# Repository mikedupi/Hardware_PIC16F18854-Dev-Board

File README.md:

# Hardware_PIC16F18854-Dev-Board
Desgined using KiCAD and designed for production at JLCPCB, with part numbers included from LCSC this board can be dropped into JLC's portal and delivered fully populated.

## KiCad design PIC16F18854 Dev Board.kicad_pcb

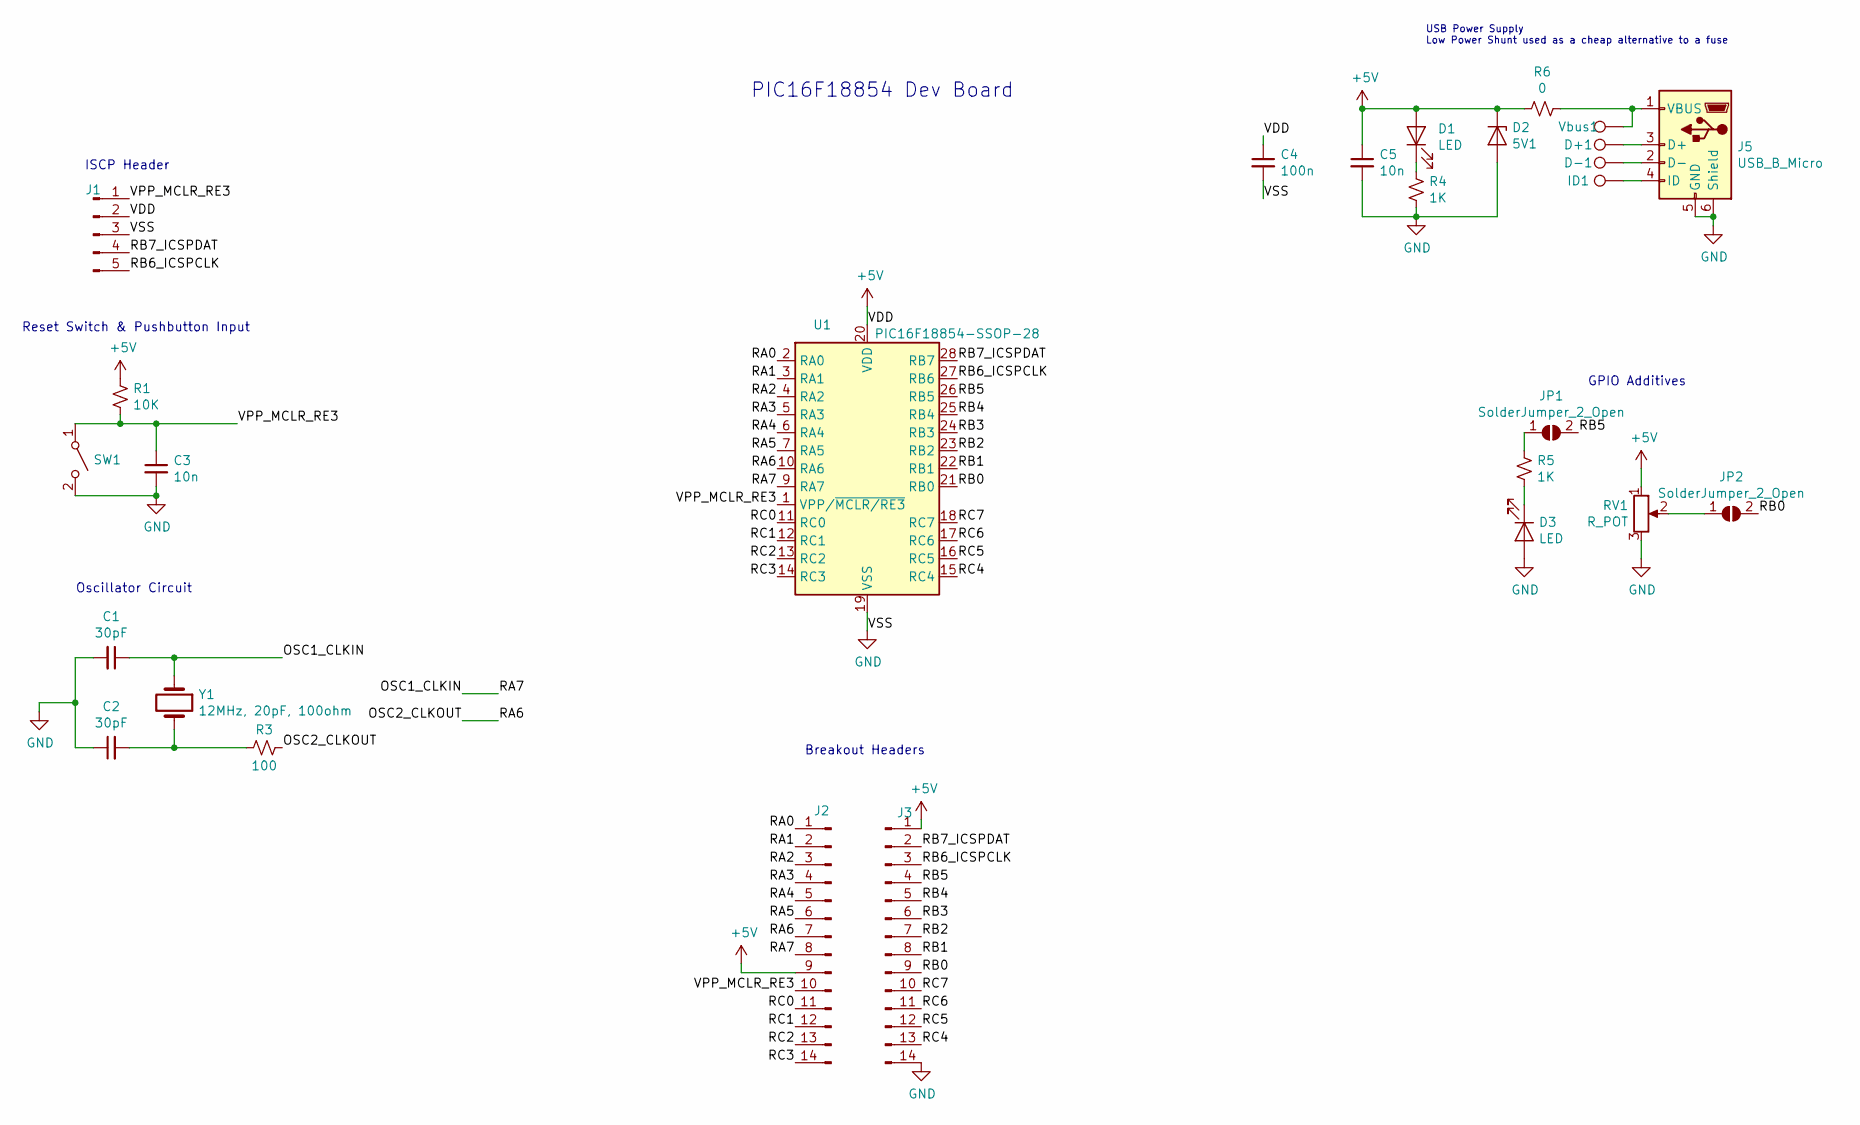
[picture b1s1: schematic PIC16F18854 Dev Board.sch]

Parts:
C1, C2: 30pF; C_0402_1005Metric; LCSC C1570
C3, C5: 10n; C_0402_1005Metric; LCSC C15195
C4: 100n; C_0402_1005Metric; LCSC C1525
D1, D3: LED; LED_0805_2012Metric; LCSC C2297
D2: 5V1; D_MiniMELF
D+1: TestPoint; TestPoint_Pad_D1.0mm
D-1: TestPoint; TestPoint_Pad_D1.0mm
ID1: TestPoint; TestPoint_Pad_D1.0mm
J1: Conn_01x05_Male; PinHeader_1x05_P2.54mm_Vertical
J2, J3: Conn_01x14_Male; PinHeader_1x14_P2.54mm_Vertical
J5: USB_B_Micro; USB_Micro-B_Amphenol_10103594-0001LF_Horizontal; LCSC C132563
JP1, JP2: SolderJumper_2_Open; SolderJumper-2_P1.3mm_Open_Pad1.0x1.5mm
R1: 10K; R_0402_1005Metric; LCSC C25744
R3: 100; R_0402_1005Metric; LCSC C25076
R4, R5: 1K; R_0402_1005Metric; LCSC C11702
R6: 0; R_0402_1005Metric; LCSC C17168
RV1: R_POT; Potentiometer_ACP_CA9-H2,5_Horizontal
SW1: SW_SPST; SW_PUSH_6mm_H5mm
U1: PIC16F18854-SSOP-28; SSOP-28_5.3x10.2mm_P0.65mm; LCSC C470935
Vbus1: TestPoint; TestPoint_Pad_D1.0mm
Y1: 12MHz, 20pF, 100ohm; Crystal_SMD_3225-2Pin_4Leg_3.2x2.5mm; LCSC C97242

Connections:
+5V: C4.1, C5.1, D1.2 (A), D2.1 (K), J1.2, J2.9, J3.1, R1.1, R6.2, RV1.1, U1.20 (VDD)
/OSC1_CLKIN: C1.1, J2.8, U1.9 (RA7), Y1.1
/OSC2_CLKOUT: J2.7, R3.1, U1.10 (RA6)
/RA0: J2.1, U1.2 (RA0)
/RA1: J2.2, U1.3 (RA1)
/RA2: J2.3, U1.4 (RA2)
/RA3: J2.4, U1.5 (RA3)
/RA4: J2.5, U1.6 (RA4)
/RA5: J2.6, U1.7 (RA5)
/RB0: J3.9, JP2.2 (B), U1.21 (RB0); also elsewhere on the board
/RB1: J3.8, U1.22 (RB1)
/RB2: J3.7, U1.23 (RB2)
/RB3: J3.6, U1.24 (RB3)
/RB4: J3.5, U1.25 (RB4)
/RB5: J3.4, JP1.2 (B), U1.26 (RB5); also elsewhere on the board
/RB6_ICSPCLK: J1.5, J3.3, U1.27 (RB6)
/RB7_ICSPDAT: J1.4, J3.2, U1.28 (RB7)
/RC0: J2.11, U1.11 (RC0)
/RC1: J2.12, U1.12 (RC1)
/RC2: J2.13, U1.13 (RC2)
/RC3: J2.14, U1.14 (RC3)
/RC4: J3.13, U1.15 (RC4)
/RC5: J3.12, U1.16 (RC5)
/RC6: J3.11, U1.17 (RC6)
/RC7: J3.10, U1.18 (RC7)
/VPP_MCLR_RE3: C3.1, J1.1, J2.10, R1.2, SW1.1 (A), U1.1 (VPP/~MCLR/RE3)
GND: C1.2, C2.1, C3.2, C4.2, C5.2, D2.2 (A), D3.2 (A), J1.3, J3.14, J5.5 (GND), J5.6 (Shield), R4.2, RV1.3, SW1.2 (B), U1.8 (VSS), U1.19 (VSS)
unnamed: C2.2, R3.2, Y1.2
unnamed: D1.1 (K), R4.1
unnamed: D3.1 (K), R5.2
unnamed: D+1.1, J5.3 (D+)
unnamed: D-1.1, J5.2 (D-)
unnamed: ID1.1, J5.4 (ID)
unnamed: J5.1 (VBUS), R6.1, Vbus1.1
unnamed 34: JP1.1 (A), R5.1; also elsewhere on the board
unnamed 35: JP2.1 (A), RV1.2; also elsewhere on the board

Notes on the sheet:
ISCP Header
Reset Switch & Pushbutton Input
USB Power Supply Low Power Shunt used as a cheap alternative to a fuse
GPIO Additives
Breakout Headers
Oscillator Circuit
PIC16F18854 Dev Board

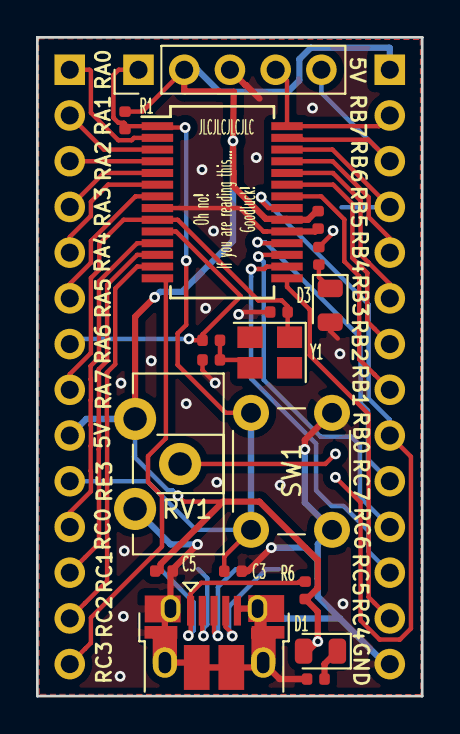
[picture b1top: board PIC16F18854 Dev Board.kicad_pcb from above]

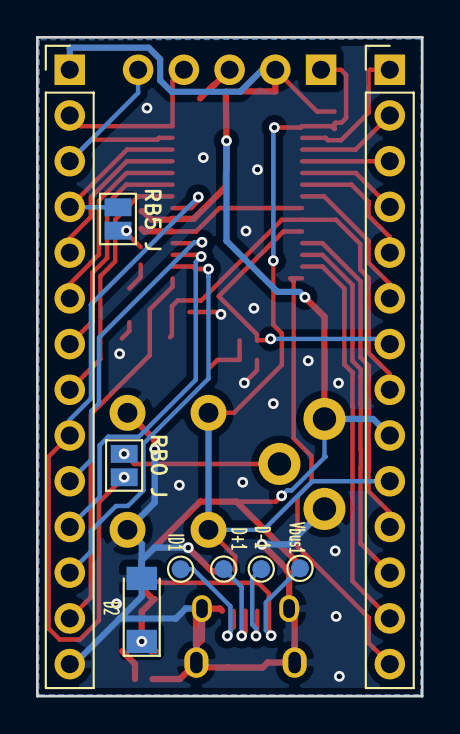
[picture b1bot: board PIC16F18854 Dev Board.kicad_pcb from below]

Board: 2 copper layers, 21.4 x 36.6 mm, 27 parts (9 on the bottom side), 36 nets.

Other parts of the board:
RB0 J, RB5 J: SolderJumper_2_Open; SolderJumper-2_P1.3mm_Open_Pad1.0x1.5mm

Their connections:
/RB0: RB0 J.2; also elsewhere on the board
/RB5: RB5 J.2; also elsewhere on the board
unnamed 34: RB5 J.1; also elsewhere on the board
unnamed 35: RB0 J.1; also elsewhere on the board

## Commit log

2021-08-01 Added Project Files
